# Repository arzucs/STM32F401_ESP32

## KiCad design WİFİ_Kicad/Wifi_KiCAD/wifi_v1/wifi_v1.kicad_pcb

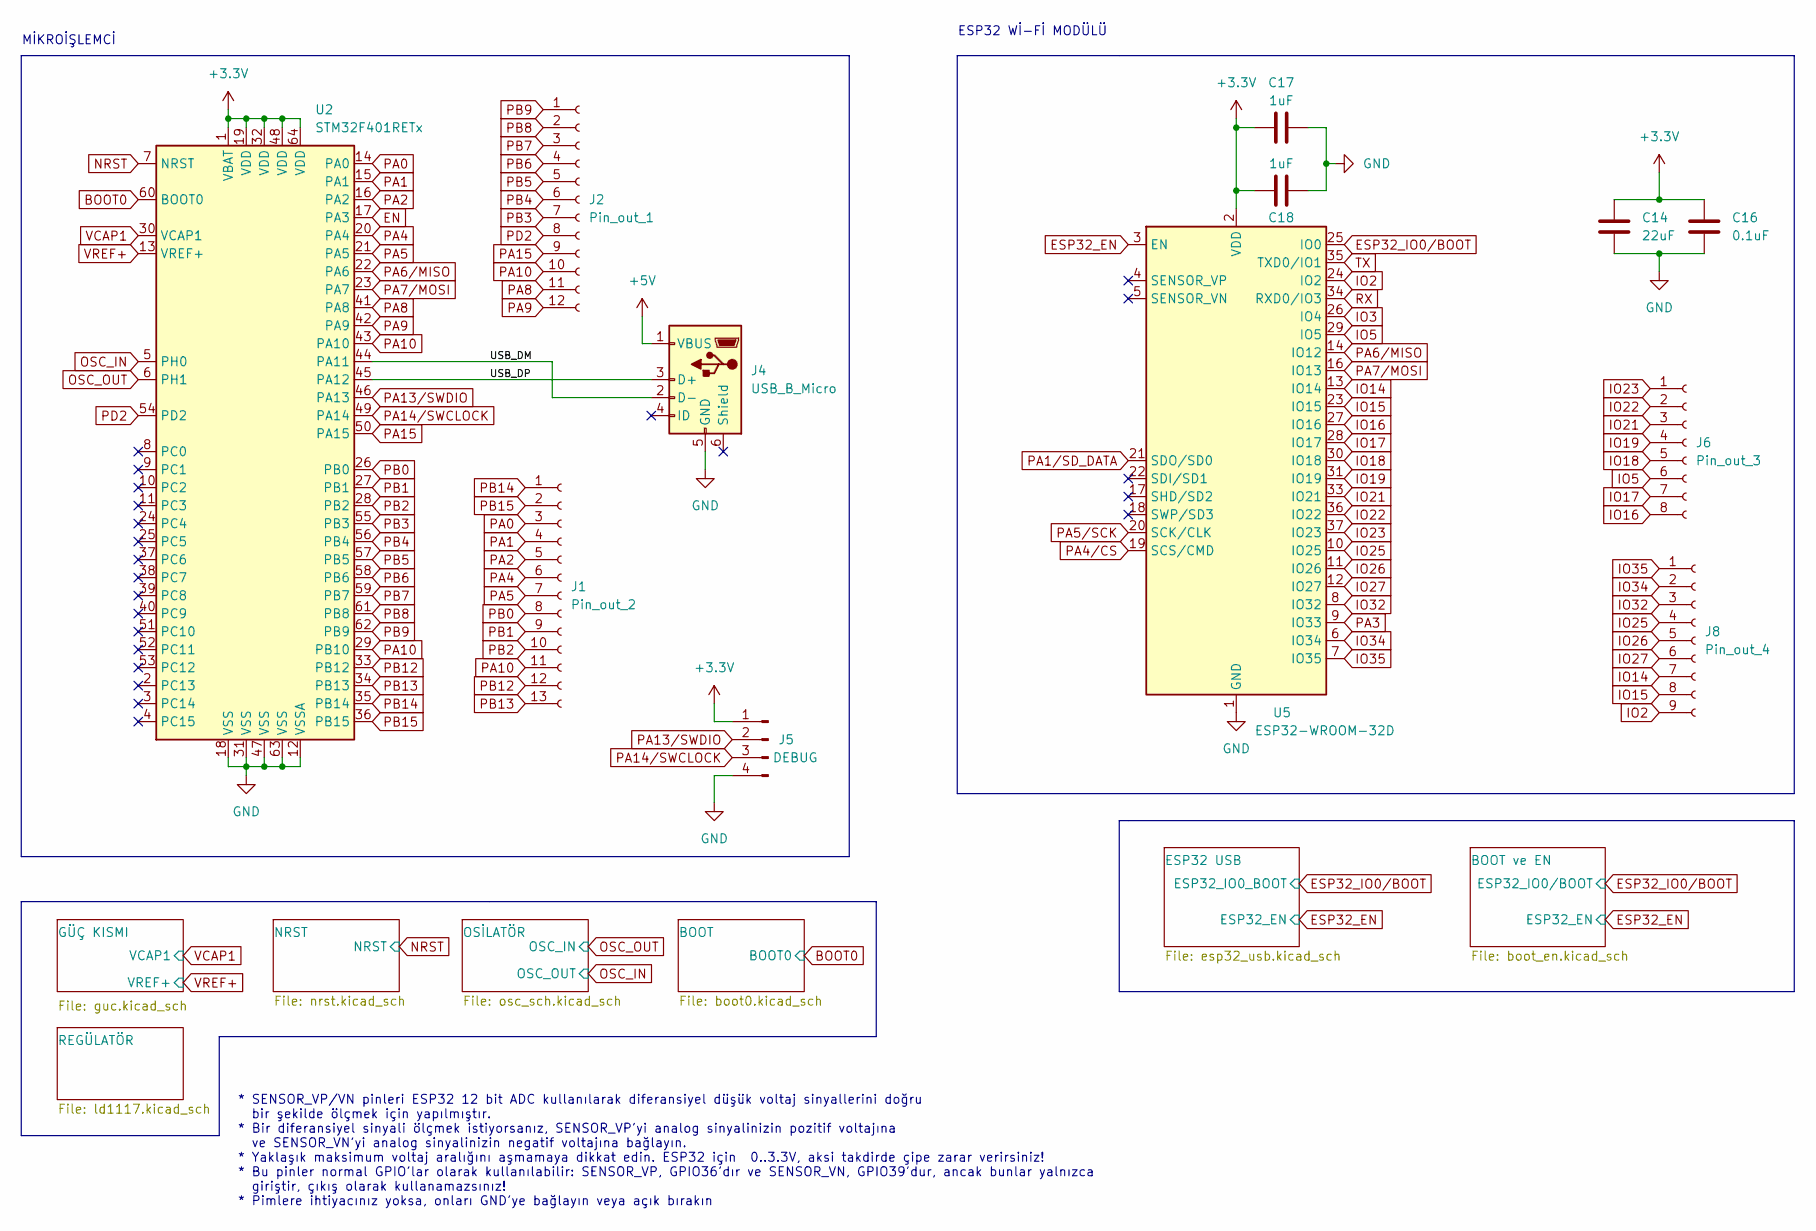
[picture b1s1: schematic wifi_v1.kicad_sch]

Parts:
C14: 22uF; C_0603_1608Metric_Pad1.08x0.95mm_HandSolder
C16: 0.1uF; C_0603_1608Metric_Pad1.08x0.95mm_HandSolder
C17, C18: 1uF; C_0603_1608Metric_Pad1.08x0.95mm_HandSolder
J1: Pin_out_2; PinHeader_1x13_P2.54mm_Vertical
J2: Pin_out_1; PinHeader_1x12_P2.54mm_Vertical
J4: USB_B_Micro; USB_Mini-B_Lumberg_2486_01_Horizontal
J5: DEBUG; PinSocket_1x04_P1.27mm_Vertical
J6: Pin_out_3; PinHeader_1x08_P2.54mm_Vertical
J8: Pin_out_4; PinHeader_1x09_P2.54mm_Vertical
U2: STM32F401RETx; LQFP-64_10x10mm_P0.5mm
U5: ESP32-WROOM-32D; ESP32-WROOM-32

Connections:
+3.3V: C14.1, C16.1, C17.2, C18.2, J5.1, U2.1 (VBAT), U2.19 (VDD), U2.32 (VDD), U2.48 (VDD), U2.64 (VDD), U5.2 (VDD); also elsewhere on the board
+5V: J4.1 (VBUS); also elsewhere on the board
/USB_DM: J4.2 (D-), U2.44 (PA11)
/USB_DP: J4.3 (D+), U2.45 (PA12)
BOOT0: U2.60 (BOOT0); also elsewhere on the board
EN: U2.17 (PA3)
ESP32_EN: U5.3 (EN); also elsewhere on the board
ESP32_IO0/BOOT: U5.25 (IO0); also elsewhere on the board
GND: C14.2, C16.2, C17.1, C18.1, J4.5 (GND), J5.4, U2.12 (VSSA), U2.18 (VSS), U2.31 (VSS), U2.47 (VSS), U2.63 (VSS), U5.1 (GND), U5.15 (GND), U5.38 (GND), U5.39 (GND); also elsewhere on the board
IO2: J8.9, U5.24 (IO2)
IO3: U5.26 (IO4)
IO5: J6.6, U5.29 (IO5)
IO14: J8.7, U5.13 (IO14)
IO15: J8.8, U5.23 (IO15)
IO16: J6.8, U5.27 (IO16)
IO17: J6.7, U5.28 (IO17)
IO18: J6.5, U5.30 (IO18)
IO19: J6.4, U5.31 (IO19)
IO21: J6.3, U5.33 (IO21)
IO22: J6.2, U5.36 (IO22)
IO23: J6.1, U5.37 (IO23)
IO25: J8.4, U5.10 (IO25)
IO26: J8.5, U5.11 (IO26)
IO27: J8.6, U5.12 (IO27)
IO32: J8.3, U5.8 (IO32)
IO34: J8.2, U5.6 (IO34)
IO35: J8.1, U5.7 (IO35)
NRST: U2.7 (NRST); also elsewhere on the board
OSC_IN: U2.5 (PH0); also elsewhere on the board
OSC_OUT: U2.6 (PH1); also elsewhere on the board
PA0: J1.3, U2.14 (PA0)
PA1: J1.4, U2.15 (PA1)
PA1/SD_DATA: U5.21 (SDO/SD0)
PA2: J1.5, U2.16 (PA2)
PA3: U5.9 (IO33)
PA4: J1.6, U2.20 (PA4)
PA4/CS: U5.19 (SCS/CMD)
PA5: J1.7, U2.21 (PA5)
PA5/SCK: U5.20 (SCK/CLK)
PA6/MISO: U2.22 (PA6), U5.14 (IO12)
PA7/MOSI: U2.23 (PA7), U5.16 (IO13)
PA8: J2.11, U2.41 (PA8)
PA9: J2.12, U2.42 (PA9)
PA10: J1.11, J2.10, U2.29 (PB10), U2.43 (PA10)
PA13/SWDIO: J5.2, U2.46 (PA13)
PA14/SWCLOCK: J5.3, U2.49 (PA14)
PA15: J2.9, U2.50 (PA15)
PB0: J1.8, U2.26 (PB0)
PB1: J1.9, U2.27 (PB1)
PB2: J1.10, U2.28 (PB2)
PB3: J2.7, U2.55 (PB3)
PB4: J2.6, U2.56 (PB4)
PB5: J2.5, U2.57 (PB5)
PB6: J2.4, U2.58 (PB6)
PB7: J2.3, U2.59 (PB7)
PB8: J2.2, U2.61 (PB8)
PB9: J2.1, U2.62 (PB9)
PB12: J1.12, U2.33 (PB12)
PB13: J1.13, U2.34 (PB13)
PB14: J1.1, U2.35 (PB14)
PB15: J1.2, U2.36 (PB15)
PD2: J2.8, U2.54 (PD2)
RX: U5.34 (RXD0/IO3); also elsewhere on the board
TX: U5.35 (TXD0/IO1); also elsewhere on the board
VCAP1: U2.30 (VCAP1); also elsewhere on the board
VREF+: U2.13 (VREF+); also elsewhere on the board

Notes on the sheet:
ESP32 Wİ-Fİ MODÜLÜ
MİKROİŞLEMCİ
* SENSOR_VP/VN pinleri ESP32 12 bit ADC kullanılarak diferansiyel düşük voltaj sinyallerini doğru bir şekilde ölçmek için yapılmıştır. * Bir diferansiyel sinyali ölçmek istiyorsanız, SENSOR_VP'yi analog sinyalinizin pozitif voltajına ve SENSOR_VN'yi analog sinyalinizin negatif voltajına bağlayın. *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

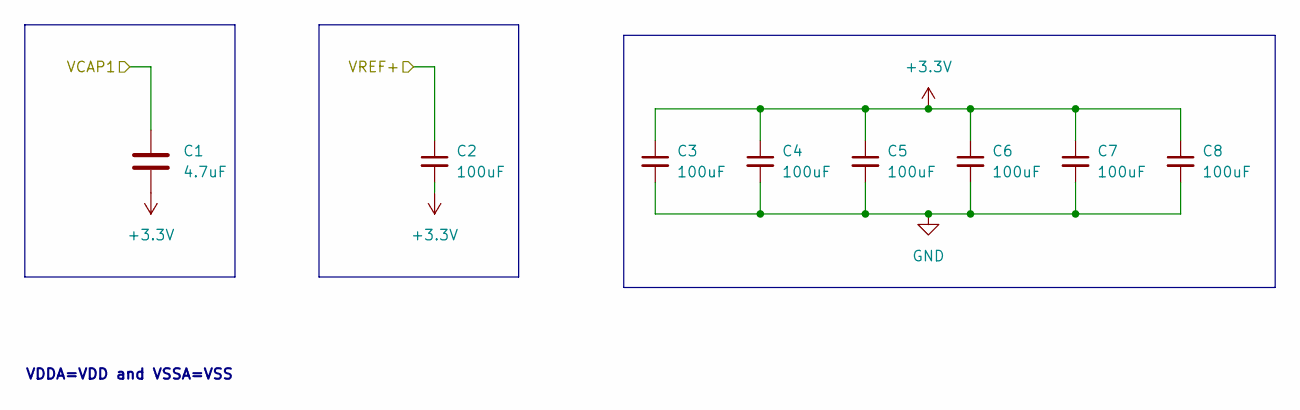
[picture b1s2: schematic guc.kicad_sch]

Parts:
C1: 4.7uF; C_0603_1608Metric_Pad1.08x0.95mm_HandSolder
C2, C3, C4, C5, C6, C7, C8: 100uF; C_0603_1608Metric_Pad1.08x0.95mm_HandSolder

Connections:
+3.3V: C1.2, C2.2, C3.1, C4.1, C5.1, C6.1, C7.1, C8.1; also elsewhere on the board
GND: C3.2, C4.2, C5.2, C6.2, C7.2, C8.2; also elsewhere on the board
VCAP1: C1.1; also elsewhere on the board
VREF+: C2.1; also elsewhere on the board

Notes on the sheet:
VDDA=VDD and VSSA=VSS

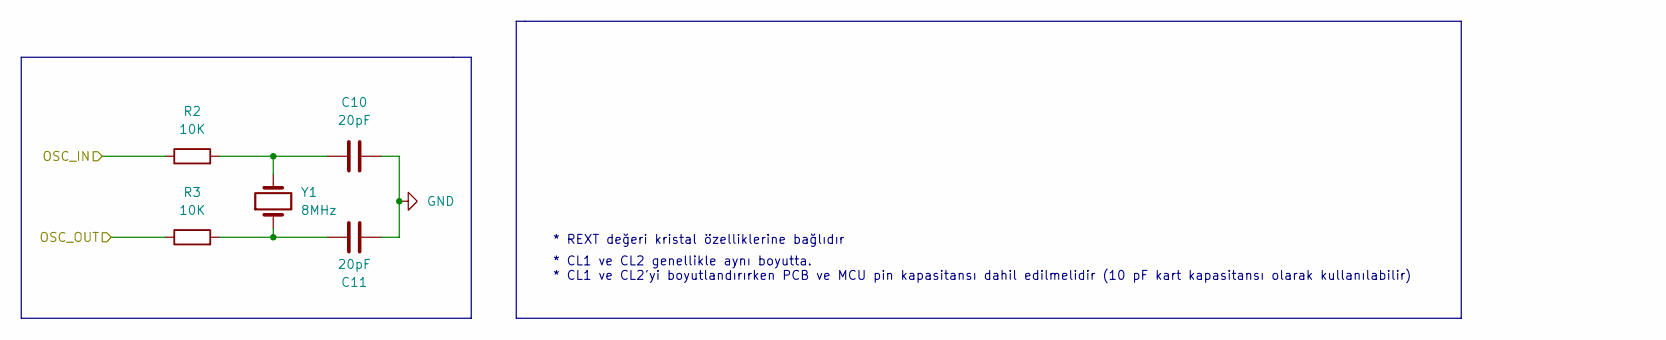
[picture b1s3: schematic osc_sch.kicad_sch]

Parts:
C10, C11: 20pF; C_0603_1608Metric_Pad1.08x0.95mm_HandSolder
R2, R3: 10K; R_0603_1608Metric_Pad0.98x0.95mm_HandSolder
Y1: 8MHz; Crystal_HC49-4H_Vertical

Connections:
GND: C10.2, C11.2; also elsewhere on the board
unnamed: C10.1, R2.2, Y1.2
unnamed: C11.1, R3.2, Y1.1
OSC_IN: R3.1; also elsewhere on the board
OSC_OUT: R2.1; also elsewhere on the board

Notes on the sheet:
* REXT değeri kristal özelliklerine bağlıdır
* CL1 ve CL2 genellikle aynı boyutta. * CL1 ve CL2'yi boyutlandırırken PCB ve MCU pin kapasitansı dahil edilmelidir (10 pF kart kapasitansı olarak kullanılabilir)

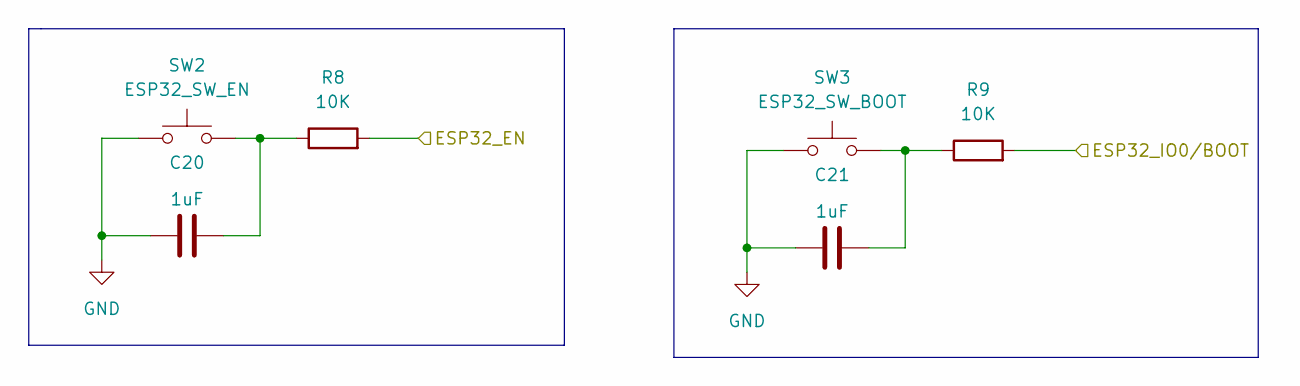
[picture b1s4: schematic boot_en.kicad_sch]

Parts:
C20, C21: 1uF; C_0603_1608Metric_Pad1.08x0.95mm_HandSolder
R8, R9: 10K; R_0603_1608Metric_Pad0.98x0.95mm_HandSolder
SW2: ESP32_SW_EN; SW_SPST_B3U-1000P-B
SW3: ESP32_SW_BOOT; SW_SPST_B3U-1000P-B

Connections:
ESP32_EN: R8.2; also elsewhere on the board
ESP32_IO0/BOOT: R9.2; also elsewhere on the board
GND: C20.2, C21.2, SW2.1, SW3.1; also elsewhere on the board
unnamed: C20.1, R8.1, SW2.2
unnamed: C21.1, R9.1, SW3.2

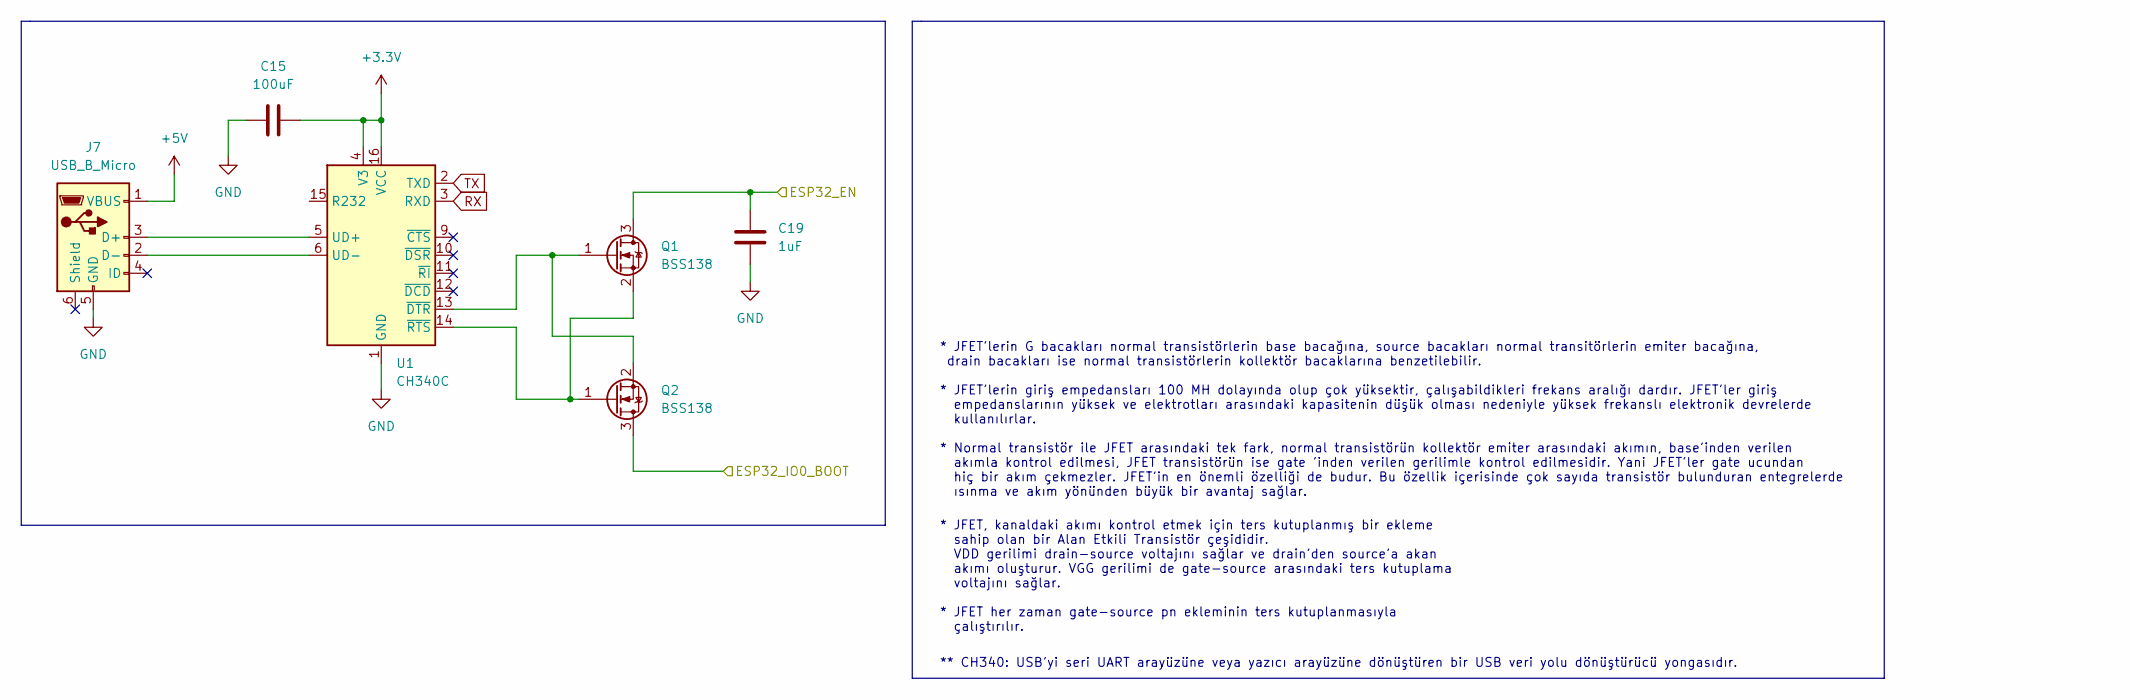
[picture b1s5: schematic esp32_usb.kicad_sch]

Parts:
C15: 100uF; C_0603_1608Metric_Pad1.08x0.95mm_HandSolder
C19: 1uF; C_0603_1608Metric_Pad1.08x0.95mm_HandSolder
J7: USB_B_Micro; USB_Mini-B_Lumberg_2486_01_Horizontal
Q1, Q2: BSS138; SOT-23
U1: CH340C; SOIC-16_3.9x9.9mm_P1.27mm

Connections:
+3.3V: C15.2, U1.4 (V3), U1.16 (VCC); also elsewhere on the board
+5V: J7.1 (VBUS); also elsewhere on the board
ESP32_EN: C19.1, Q1.3 (D); also elsewhere on the board
ESP32_IO0/BOOT: Q2.3 (D); also elsewhere on the board
GND: C15.1, C19.2, J7.5 (GND), U1.1 (GND); also elsewhere on the board
unnamed: J7.2 (D-), U1.6 (UD-)
unnamed: J7.3 (D+), U1.5 (UD+)
unnamed: Q1.1 (G), Q2.2 (S), U1.13 (~DTR)
unnamed: Q1.2 (S), Q2.1 (G), U1.14 (~RTS)
RX: U1.3 (RXD); also elsewhere on the board
TX: U1.2 (TXD); also elsewhere on the board

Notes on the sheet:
* JFET, kanaldaki akımı kontrol etmek için ters kutuplanmış bir ekleme sahip olan bir Alan Etkili Transistör çeşididir. VDD gerilimi drain-source voltajını sağlar ve drain'den source'a akan akımı oluşturur. VGG gerilimi de gate-source arasındaki ters kutuplama voltajını sağlar. * JFET her zaman gat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
* JFET'lerin G bacakları normal transistörlerin base bacağına, source bacakları normal transitörlerin emiter bacağına, drain bacakları ise normal transistörlerin kollektör bacaklarına benzetilebilir. * JFET'lerin giriş empedansları 100 MH dolayında olup çok yüksektir, çalışabildikleri frekans aralı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
** CH340: USB'yi seri UART arayüzüne veya yazıcı arayüzüne dönüştüren bir USB veri yolu dönüştürücü yongasıdır.

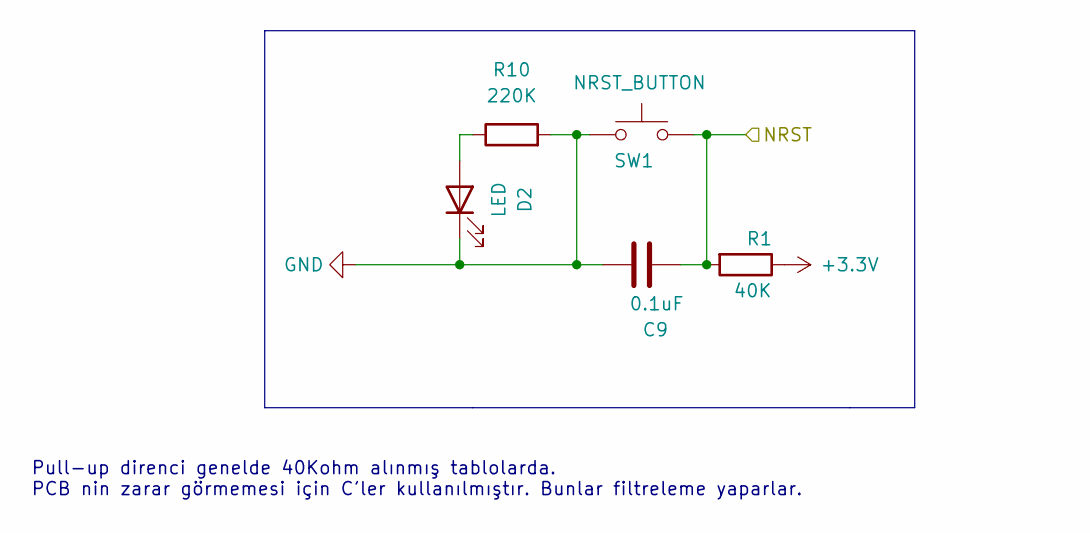
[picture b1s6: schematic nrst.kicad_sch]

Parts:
C9: 0.1uF; C_0603_1608Metric_Pad1.08x0.95mm_HandSolder
D2: LED; LED_0805_2012Metric_Pad1.15x1.40mm_HandSolder
R1: 40K; R_0603_1608Metric_Pad0.98x0.95mm_HandSolder
R10: 220K; R_0603_1608Metric_Pad0.98x0.95mm_HandSolder
SW1: NRST_BUTTON; SW_SPST_B3U-1000P-B

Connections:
+3.3V: R1.1; also elsewhere on the board
GND: C9.1, D2.1 (K), R10.2, SW1.1; also elsewhere on the board
NRST: C9.2, R1.2, SW1.2; also elsewhere on the board
unnamed: D2.2 (A), R10.1

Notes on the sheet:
Pull-up direnci genelde 40Kohm alınmış tablolarda. PCB nin zarar görmemesi için C'ler kullanılmıştır. Bunlar filtreleme yaparlar.

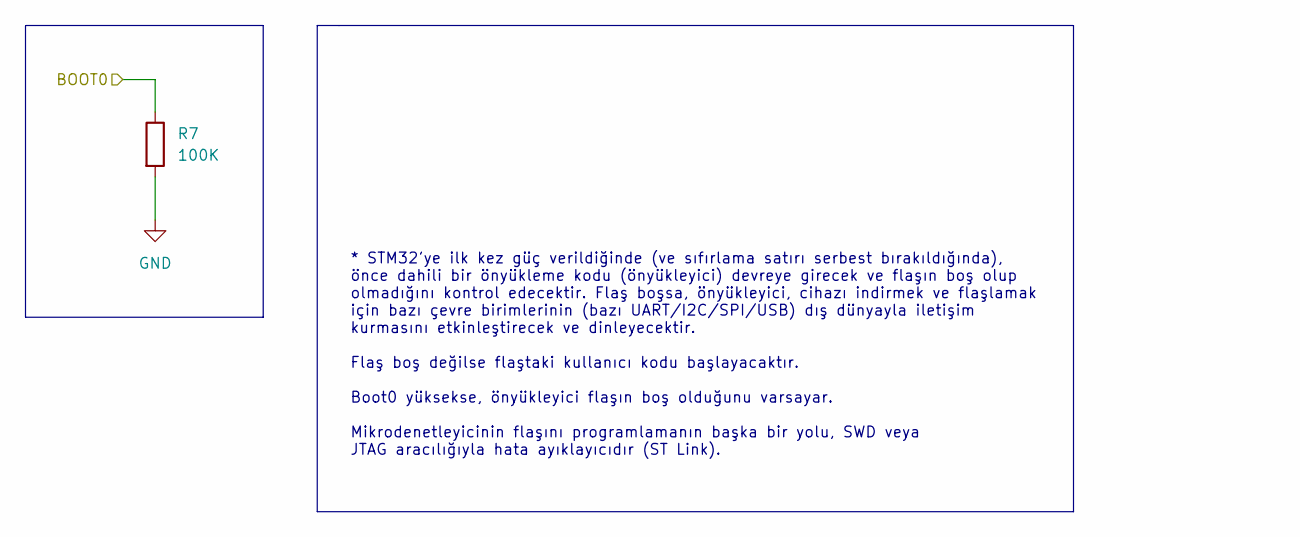
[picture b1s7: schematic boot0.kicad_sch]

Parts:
R7: 100K; R_0603_1608Metric_Pad0.98x0.95mm_HandSolder

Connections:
BOOT0: R7.1; also elsewhere on the board
GND: R7.2; also elsewhere on the board

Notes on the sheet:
* STM32'ye ilk kez güç verildiğinde (ve sıfırlama satırı serbest bırakıldığında), önce dahili bir önyükleme kodu (önyükleyici) devreye girecek ve flaşın boş olup olmadığını kontrol edecektir. Flaş boşsa, önyükleyici, cihazı indirmek ve flaşlamak için bazı çevre birimlerinin (bazı UART/I2C/SPI/USB) 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

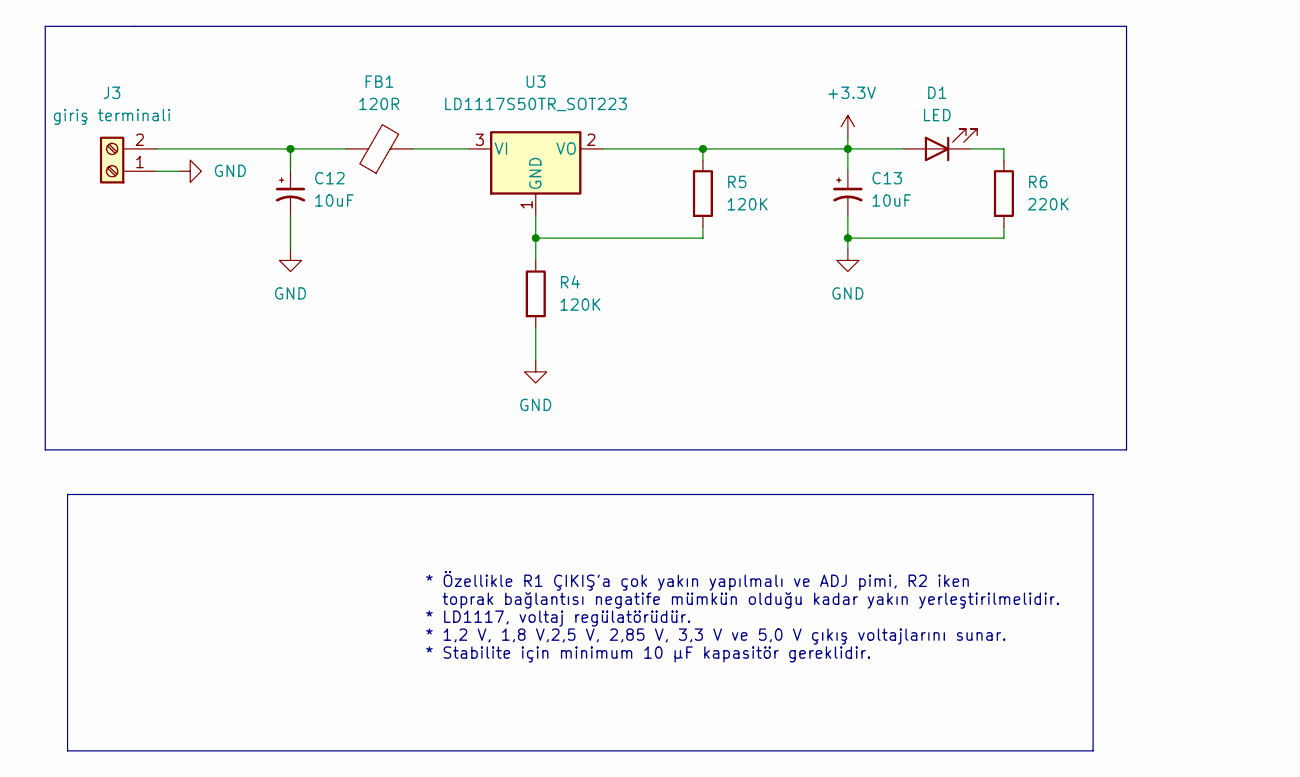
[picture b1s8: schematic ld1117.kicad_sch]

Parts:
C12, C13: 10uF; CP_Elec_5x3
D1: LED; LED_0805_2012Metric_Pad1.15x1.40mm_HandSolder
FB1: 120R; L_0805_2012Metric_Pad1.15x1.40mm_HandSolder
J3: giriş terminali; TerminalBlock_Phoenix_MKDS-1,5-2-5.08_1x02_P5.08mm_Horizont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
R4, R5: 120K; R_0603_1608Metric_Pad0.98x0.95mm_HandSolder
R6: 220K; R_0603_1608Metric_Pad0.98x0.95mm_HandSolder
U3: LD1117S50TR_SOT223; SOT-223-3_TabPin2

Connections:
+3.3V: C13.1, D1.2 (A), R5.1, U3.2 (VO); also elsewhere on the board
GND: C12.2, C13.2, J3.1, R4.2, R6.2; also elsewhere on the board
unnamed: C12.1, FB1.1, J3.2
unnamed: D1.1 (K), R6.1
unnamed: FB1.2, U3.3 (VI)
unnamed: R4.1, R5.2, U3.1 (GND)

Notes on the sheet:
* Özellikle R1 ÇIKIŞ'a çok yakın yapılmalı ve ADJ pimi, R2 iken toprak bağlantısı negatife mümkün olduğu kadar yakın yerleştirilmelidir. * LD1117, voltaj regülatörüdür. * 1,2 V, 1,8 V,2,5 V, 2,85 V, 3,3 V ve 5,0 V çıkış voltajlarını sunar. * Stabilite için minimum 10 µF kapasitör gereklidir.

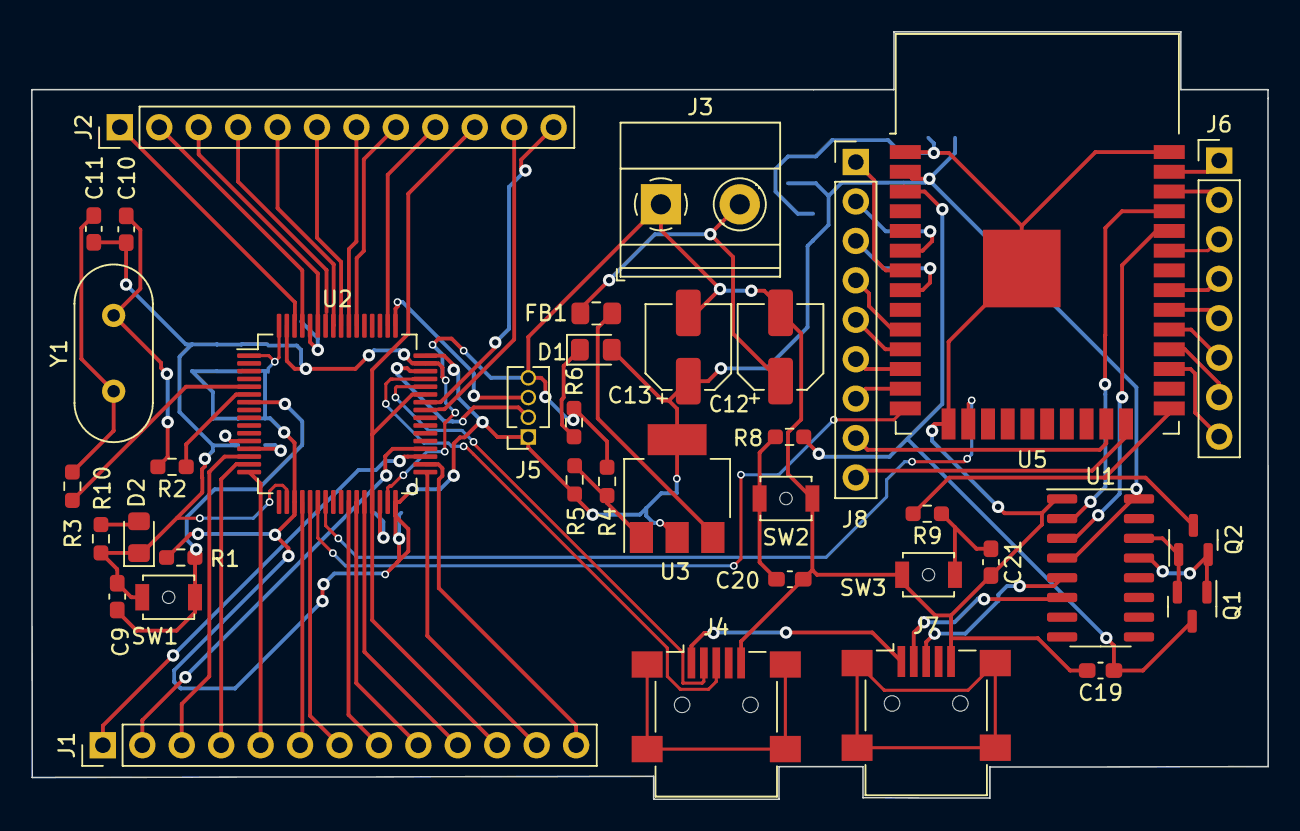
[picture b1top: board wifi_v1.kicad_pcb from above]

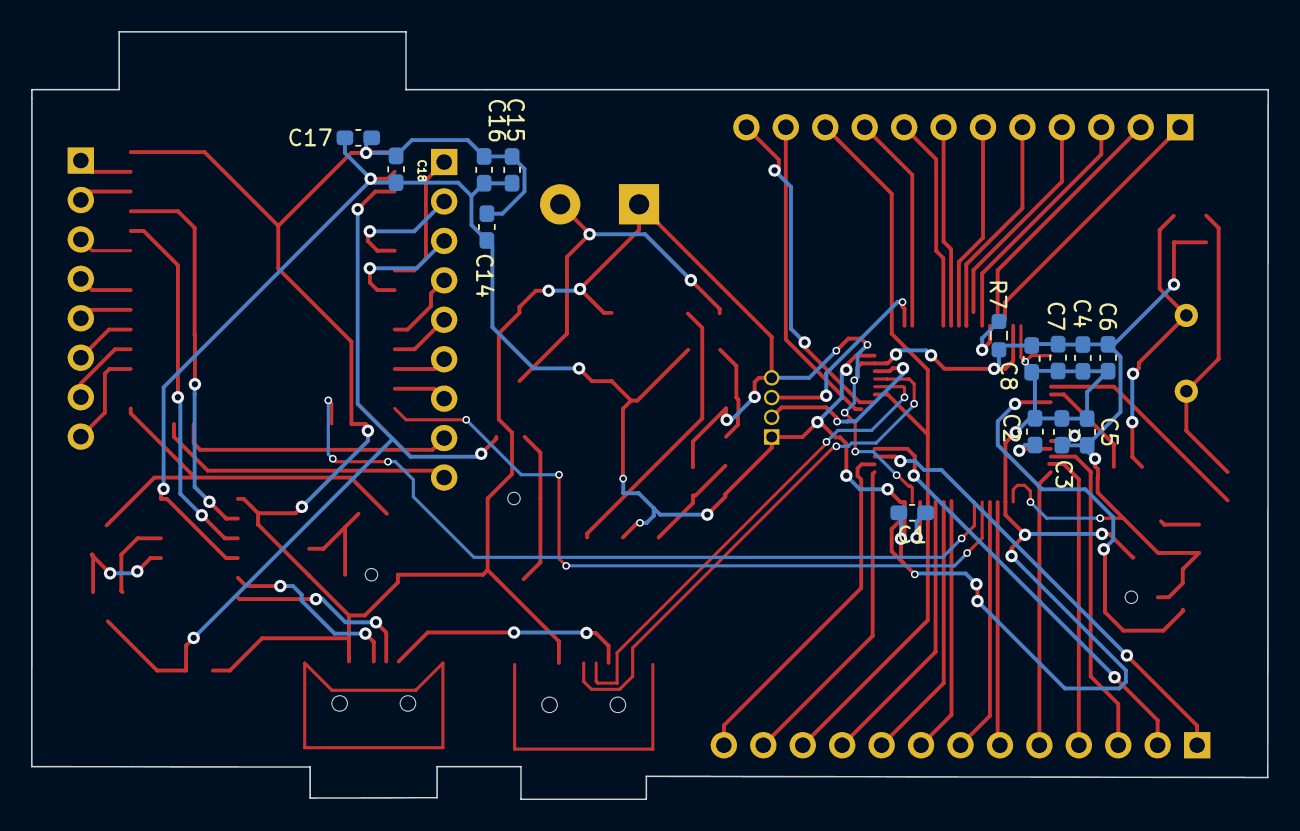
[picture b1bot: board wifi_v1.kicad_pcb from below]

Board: 2 copper layers, 79.6 x 49.4 mm, 52 parts (14 on the bottom side), 73 nets.

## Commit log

2023-02-25 stm32 ve esp32
    STM32F401 Nucleo kartı ile ESP32 Wİ-Fİ modülü olan pcb çizimi.
